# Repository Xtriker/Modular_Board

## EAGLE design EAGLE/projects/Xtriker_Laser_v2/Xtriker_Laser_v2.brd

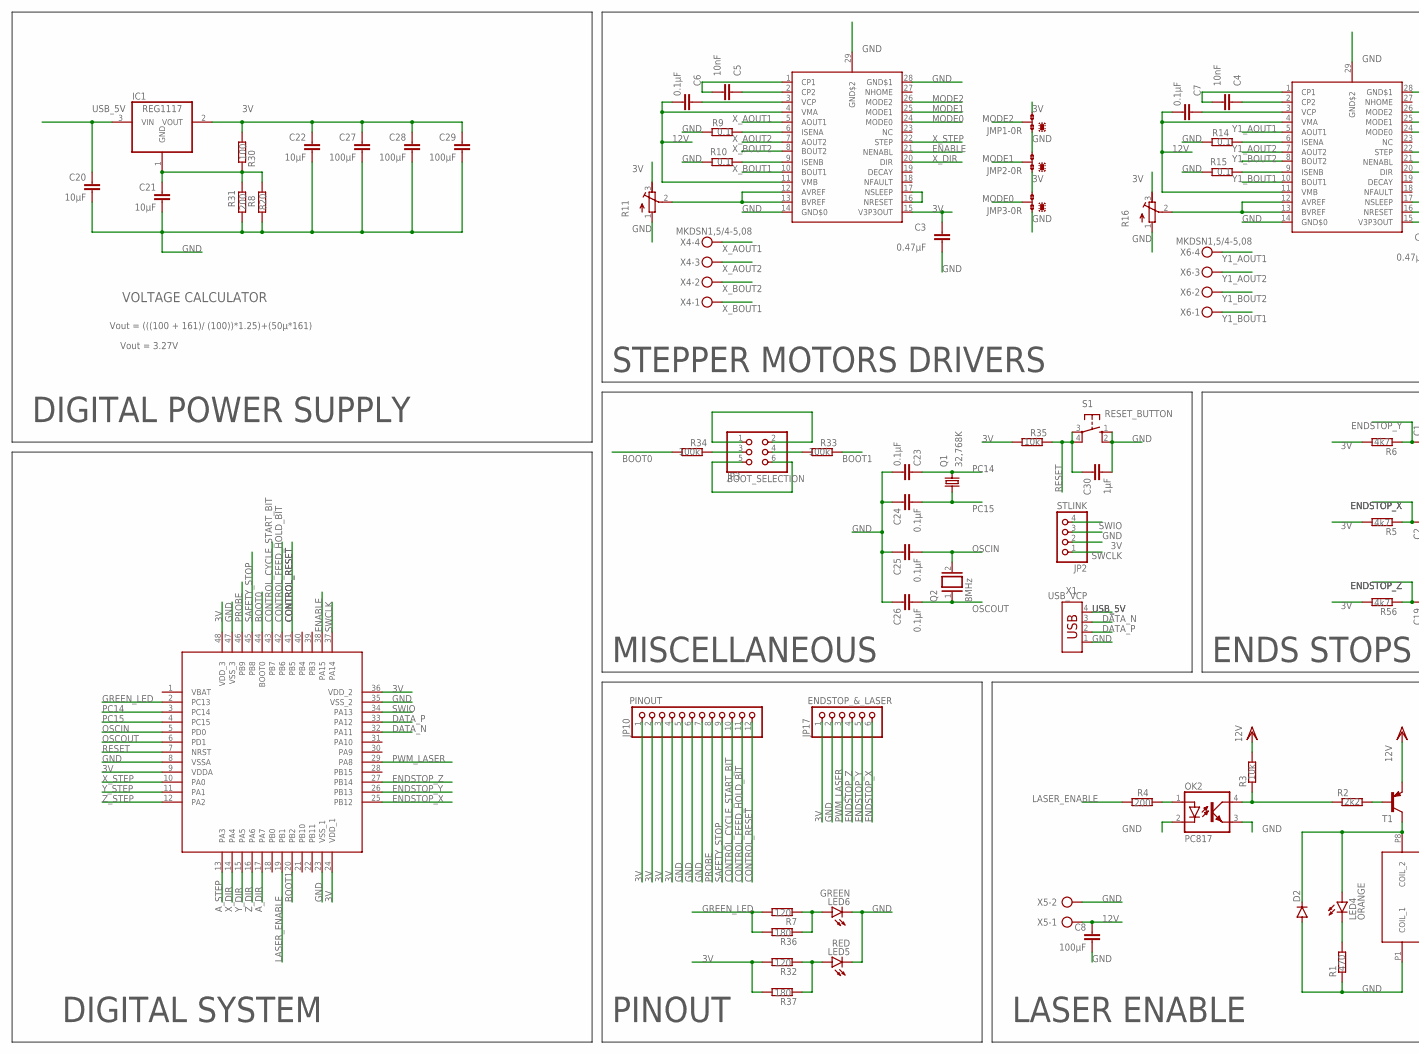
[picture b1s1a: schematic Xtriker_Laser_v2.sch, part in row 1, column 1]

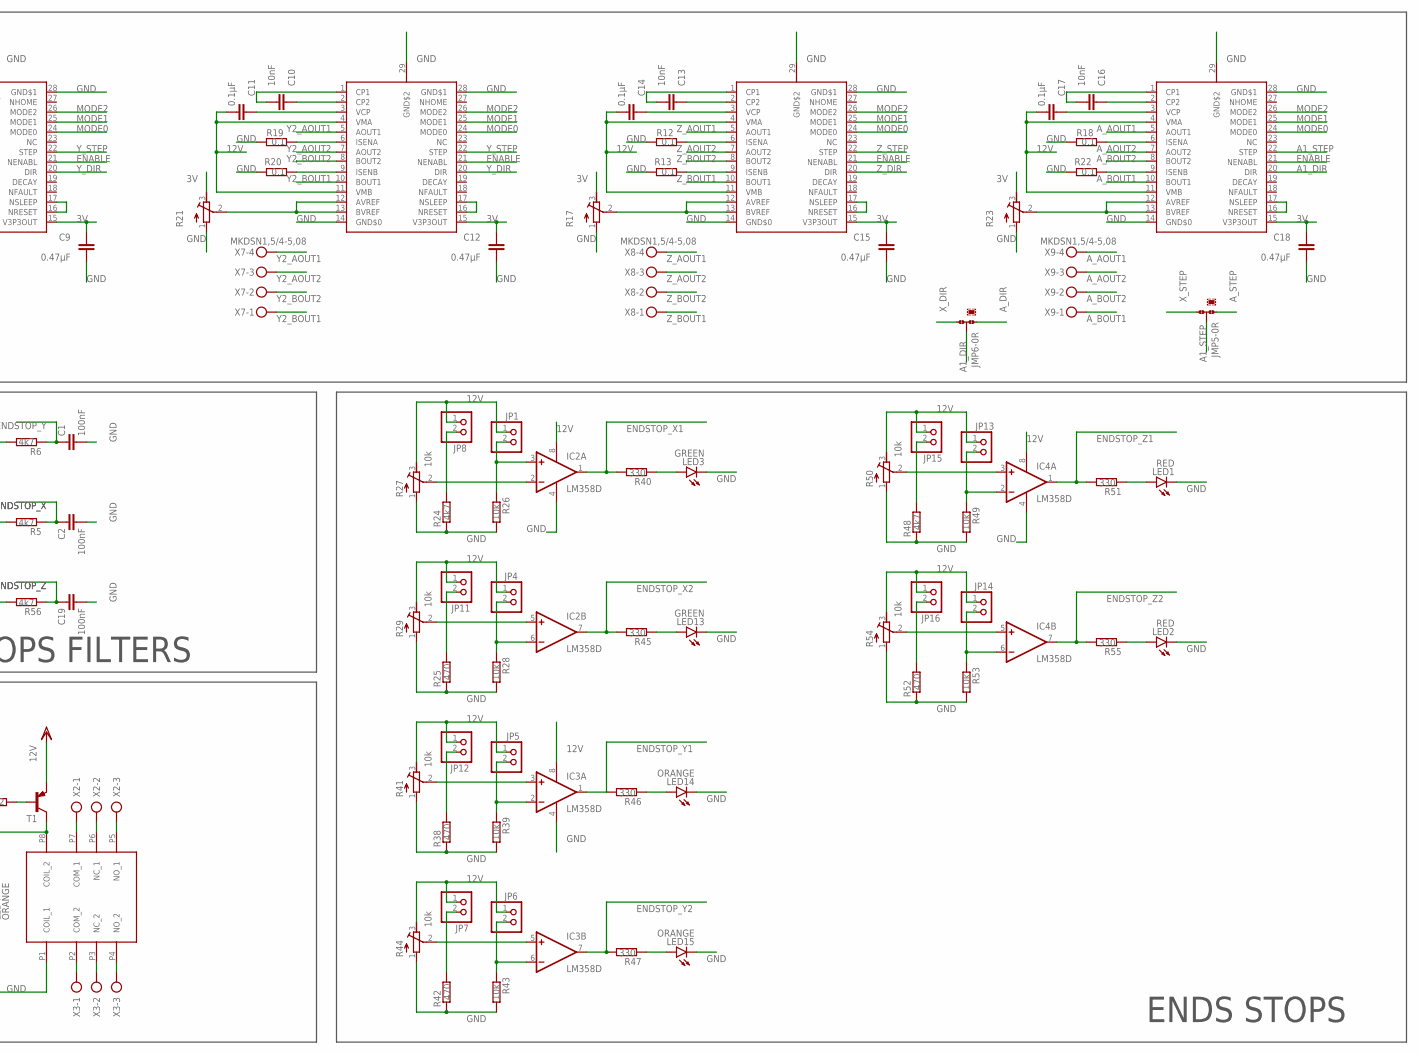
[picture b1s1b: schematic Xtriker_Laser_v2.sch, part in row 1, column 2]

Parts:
C1, C2, C19: 100nF; C0805
C3, C9, C12, C15, C18: 0.47µF; C0805
C4, C5, C10, C13, C16: 10nF; C0805
C6, C7, C11, C14, C17, C23, C24, C25, C26: 0.1µF; C0805
C8, C27, C28, C29: 100µF; C0805
C20, C21, C22: 10µF; C0805
C30: 1µF; C0805
D2: DIODE-DO214AA; DO214AA
IC1: REG1117; SOT223
IC2, IC3, IC4: LM358D; SO08
JMP1, JMP2, JMP3, JMP5, JMP6: 0R-JUMPA; A0R-JMP
JP1, JP4, JP5, JP6, JP7, JP8, JP11, JP12, JP13, JP14, JP15, JP16: PINHD-1X2; 1X02
JP2: STLINK; 1X04
JP3: BOOT_SELECTION; 2X03
JP10: PINOUT; 1X12
JP17: ENDSTOP_&_LASER; 1X06
LED1, LED2, LED5: RED; CHIP-LED0805
LED3, LED6, LED13: GREEN; CHIP-LED0805
LED4, LED14, LED15: ORANGE; CHIP-LED0805
OK2: PC817; DIL04
Q1: 32,768K; 8.2X3.8
Q2: 8MHz; QS
R1, R25, R38, R42, R52: 470; R0805
R2: 2k2; R0805
R3, R26, R28, R35, R39, R43, R49, R53: 10k; R0805
R4, R31: 200; R0805
R5, R6, R24, R48, R56: 4k7; R0805
R7, R32: 120; R0805
R8: 820; R0805
R9, R10, R12, R13, R14, R15, R18, R19, R20, R22: 0.1; R2512
R11, R16, R17, R21, R23: R-TRIMM3296W; RTRIM3296W
R27, R29, R41, R44, R50, R54: 10k; RTRIM3296W
R30: 100; R0805
R33, R34: 100k; R0805
R36, R37: 180; R0805
R40, R45, R46, R47, R51, R55: 330; R0805
S1: RESET_BUTTON; B3F-10XX
T1: -PNP-SOT23-BCE; SOT23-BCE
U$1, U$2, U$3, U$4, U$7: DRV8825; SOP65P660X135-29T310X518N
U$5: TDS-1202L; TDS_1202L
U$6: STM32F103C8_LQFP48; QFP50P900X900X160-48N
X1: USB_VCP; USB
X2, X3: AK500/3
X4, X6, X7, X8, X9: MKDSN1,5/4-5,08
X5: AK500/2

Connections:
3V: C3.1, C9.1, C12.1, C15.1, C18.1, C22.1, C27.1, C28.1, C29.1, IC1.2 (VOUT), JMP1.3, JMP2.1, JMP3.3, JP2.2, JP10.1, JP10.2, JP10.3, JP10.4, JP17.1, R5.2, R6.2, R11.3 (E), R16.3 (E), R17.3 (E), R21.3 (E), R23.3 (E), R30.2, R32.2, R35.2, R37.2, R56.2, U$1.15 (V3P3OUT), U$2.15 (V3P3OUT), U$3.15 (V3P3OUT), U$4.15 (V3P3OUT), U$6.9 (VDDA), U$6.24 (VDD_1), U$6.36 (VDD_2), U$6.48 (VDD_3), U$7.15 (V3P3OUT)
12V: C6.2, C7.2, C8.1, C11.2, C14.2, C17.2, IC2.8 (V+), IC3.8 (V+), IC4.8 (V+), JP1.1, JP4.1, JP5.1, JP6.1, JP7.1, JP8.1, JP11.1, JP12.1, JP13.1, JP14.1, JP15.1, JP16.1, R27.3 (E), R29.3 (E), R41.3 (E), R44.3 (E), R50.3 (E), R54.3 (E), U$1.4 (VMA), U$1.11 (VMB), U$2.4 (VMA), U$2.11 (VMB), U$3.4 (VMA), U$3.11 (VMB), U$4.4 (VMA), U$4.11 (VMB), U$7.4 (VMA), U$7.11 (VMB), X5.1
A1_DIR: JMP6.2, U$7.20 (DIR)
A1_STEP: JMP5.2, U$7.22 (STEP)
A_AOUT1: U$7.5 (AOUT1), X9.4
A_AOUT2: U$7.7 (AOUT2), X9.3
A_BOUT1: U$7.10 (BOUT1), X9.1
A_BOUT2: U$7.8 (BOUT2), X9.2
A_DIR: JMP6.1, U$6.17 (PA7)
A_STEP: JMP5.1, U$6.13 (PA3)
BOOT0: R34.2, U$6.44 (BOOT0)
BOOT1: R33.1, U$6.20 (PB2)
CONTROL_CYCLE_START_BIT: JP10.10, U$6.43 (PB7)
CONTROL_FEED_HOLD_BIT: JP10.11, U$6.42 (PB6)
CONTROL_RESET: JP10.12, U$6.41 (PB5)
DATA_N: U$6.32 (PA11), X1.3
DATA_P: U$6.33 (PA12), X1.2
ENABLE: U$1.21 (NENABL), U$2.21 (NENABL), U$3.21 (NENABL), U$4.21 (NENABL), U$6.38 (PA15), U$7.21 (NENABL)
ENDSTOP_X: C2.1, JP17.6, R5.1, U$6.25 (PB12)
ENDSTOP_X1: IC2.1 (OUT), R40.2
ENDSTOP_X2: IC2.7 (OUT), R45.2
ENDSTOP_Y: C1.1, JP17.5, R6.1, U$6.26 (PB13)
ENDSTOP_Y1: IC3.1 (OUT), R46.2
ENDSTOP_Y2: IC3.7 (OUT), R47.2
ENDSTOP_Z: C19.1, JP17.4, R56.1, U$6.27 (PB14)
ENDSTOP_Z1: IC4.1 (OUT), R51.2
ENDSTOP_Z2: IC4.7 (OUT), R55.2
GND: C1.2, C2.2, C3.2, C8.2, C9.2, C12.2, C15.2, C18.2, C19.2, C20.2, C21.2, C22.2, C23.2, C24.1, C25.1, C26.1, C27.2, C28.2, C29.2, C30.2, D2.A, IC2.4 (V-), IC3.4 (V-), IC4.4 (V-), JMP1.1, JMP2.3, JMP3.1, JP2.3, JP10.5, JP10.6, JP10.7, JP17.2, LED1.C, LED2.C, LED3.C, LED5.C, LED6.C, LED13.C, LED14.C, LED15.C, OK2.2 (C), OK2.3 (EMIT), R1.1, R8.1, R9.1, R10.1, R11.1 (A), R12.1, R13.1, R14.1, R15.1, R16.1 (A), R17.1 (A), R18.1, R19.1, R20.1, R21.1 (A), R22.1, R23.1 (A), R24.1, R25.1, R26.2, R27.1 (A), R28.2, R29.1 (A), R31.1, R38.1, R39.2, R41.1 (A), R42.1, R43.2, R44.1 (A), R48.1, R49.2, R50.1 (A), R52.1, R53.2, R54.1 (A), S1.1 (S), S1.2 (S1), U$1.14 (GND$0), U$1.28 (GND$1), U$1.29 (GND$2), U$2.14 (GND$0), U$2.28 (GND$1), U$2.29 (GND$2), U$3.14 (GND$0), U$3.28 (GND$1), U$3.29 (GND$2), U$4.14 (GND$0), U$4.28 (GND$1), U$4.29 (GND$2), U$5.P1 (COIL_1), U$6.8 (VSSA), U$6.23 (VSS_1), U$6.35 (VSS_2), U$6.47 (VSS_3), U$7.14 (GND$0), U$7.28 (GND$1), U$7.29 (GND$2), X1.1, X5.2
GREEN_LED: R7.2, R36.2, U$6.2 (PC13)
LASER_ENABLE: R4.1, U$6.19 (PB1)
MODE0: JMP3.2, U$1.24 (MODE0), U$2.24 (MODE0), U$3.24 (MODE0), U$4.24 (MODE0), U$7.24 (MODE0)
MODE1: JMP2.2, U$1.25 (MODE1), U$2.25 (MODE1), U$3.25 (MODE1), U$4.25 (MODE1), U$7.25 (MODE1)
MODE2: JMP1.2, U$1.26 (MODE2), U$2.26 (MODE2), U$3.26 (MODE2), U$4.26 (MODE2), U$7.26 (MODE2)
unnamed: C13.2, U$4.1 (CP1)
unnamed: U$1.16 (NRESET), U$1.17 (NSLEEP)
unnamed: C4.2, U$2.1 (CP1)
unnamed: C4.1, U$2.2 (CP2)
unnamed: C7.1, U$2.3 (VCP)
unnamed: R14.2, U$2.6 (ISENA)
unnamed: R15.2, U$2.9 (ISENB)
unnamed: R16.2 (S), U$2.12 (AVREF), U$2.13 (BVREF)
unnamed: C21.1, IC1.1 (GND), R8.2, R30.1, R31.2
unnamed: LED5.A, R32.1, R37.1
unnamed: JP3.1, JP3.2
unnamed: C13.1, U$4.2 (CP2)
unnamed: D2.C, LED4.A, T1.C, U$5.P8 (COIL_2)
unnamed: LED4.C, R1.2
unnamed: R2.2, T1.B
unnamed: OK2.4 (COL), R2.1, R3.1
unnamed: OK2.1 (A), R4.2
unnamed: U$2.16 (NRESET), U$2.17 (NSLEEP)
unnamed: C10.2, U$3.1 (CP1)
unnamed: C10.1, U$3.2 (CP2)
unnamed: C11.1, U$3.3 (VCP)
unnamed: C5.2, U$1.1 (CP1)
unnamed: C5.1, U$1.2 (CP2)
unnamed: C6.1, U$1.3 (VCP)
unnamed: R19.2, U$3.6 (ISENA)
unnamed: R20.2, U$3.9 (ISENB)
unnamed: R9.2, U$1.6 (ISENA)
unnamed: R21.2 (S), U$3.12 (AVREF), U$3.13 (BVREF)
unnamed: U$5.P7 (COM_1), X2.1
unnamed: U$5.P6 (NC_1), X2.2
unnamed: U$5.P5 (NO_1), X2.3
unnamed: U$5.P4 (NO_2), X3.3
unnamed: U$5.P3 (NC_2), X3.2
unnamed: U$5.P2 (COM_2), X3.1
unnamed: LED6.A, R7.1, R36.1
unnamed: C14.1, U$4.3 (VCP)
unnamed: R10.2, U$1.9 (ISENB)
unnamed: U$3.16 (NRESET), U$3.17 (NSLEEP)
unnamed: LED3.A, R40.1
unnamed: IC2.3 (+IN), JP1.2, R26.1
unnamed: JP3.5, JP3.6
unnamed: JP3.3, R34.1
unnamed: JP3.4, R33.2
unnamed: R11.2 (S), U$1.12 (AVREF), U$1.13 (BVREF)
unnamed: JP8.2, R24.2
unnamed: IC2.6 (-IN), JP4.2, R28.1
unnamed: IC2.2 (-IN), R27.2 (S)
unnamed: JP11.2, R25.2
unnamed: IC2.5 (+IN), R29.2 (S)
unnamed: IC3.2 (-IN), JP5.2, R39.1
unnamed: JP12.2, R38.2
unnamed: IC3.3 (+IN), R41.2 (S)
unnamed: IC3.6 (-IN), JP6.2, R43.1
unnamed: JP7.2, R42.2
unnamed: IC3.5 (+IN), R44.2 (S)
unnamed: LED13.A, R45.1
unnamed: LED14.A, R46.1
unnamed: LED15.A, R47.1
unnamed: R12.2, U$4.6 (ISENA)
unnamed: R13.2, U$4.9 (ISENB)
unnamed: R17.2 (S), U$4.12 (AVREF), U$4.13 (BVREF)
unnamed: U$4.16 (NRESET), U$4.17 (NSLEEP)
unnamed: C16.2, U$7.1 (CP1)
unnamed: C16.1, U$7.2 (CP2)
unnamed: C17.1, U$7.3 (VCP)
unnamed: R18.2, U$7.6 (ISENA)
unnamed: R22.2, U$7.9 (ISENB)
unnamed: R23.2 (S), U$7.12 (AVREF), U$7.13 (BVREF)
unnamed: U$7.16 (NRESET), U$7.17 (NSLEEP)
unnamed: IC4.2 (-IN), JP13.2, R49.1
unnamed: JP15.2, R48.2
unnamed: IC4.3 (+IN), R50.2 (S)
unnamed: LED1.A, R51.1
unnamed: IC4.6 (-IN), JP14.2, R53.1
unnamed: JP16.2, R52.2
unnamed: IC4.5 (+IN), R54.2 (S)
unnamed: LED2.A, R55.1
OSCIN: C25.2, Q2.2, U$6.5 (PD0)
OSCOUT: C26.2, Q2.1, U$6.6 (PD1)
PC14: C23.1, Q1.4 (2), U$6.3 (PC14)
PC15: C24.2, Q1.1, U$6.4 (PC15)
PROBE: JP10.8, U$6.46 (PB9)
PWM_LASER: JP17.3, U$6.29 (PA8)
RESET: C30.1, R35.1, S1.3, S1.4 (P1), U$6.7 (NRST)
SAFETY_STOP: JP10.9, U$6.45 (PB8)
SWCLK: JP2.1, U$6.37 (PA14)
SWIO: JP2.4, U$6.34 (PA13)
USB_5V: C20.1, IC1.3 (VIN), X1.4
VDD: R3.2, T1.E
X_AOUT1: U$1.5 (AOUT1), X4.4
X_AOUT2: U$1.7 (AOUT2), X4.3
X_BOUT1: U$1.10 (BOUT1), X4.1
X_BOUT2: U$1.8 (BOUT2), X4.2
X_DIR: JMP6.3, U$1.20 (DIR), U$6.14 (PA4)
X_STEP: JMP5.3, U$1.22 (STEP), U$6.10 (PA0)
Y1_AOUT1: U$2.5 (AOUT1), X6.4
Y1_AOUT2: U$2.7 (AOUT2), X6.3
Y1_BOUT1: U$2.10 (BOUT1), X6.1
Y1_BOUT2: U$2.8 (BOUT2), X6.2
Y2_AOUT1: U$3.5 (AOUT1), X7.4
Y2_AOUT2: U$3.7 (AOUT2), X7.3
Y2_BOUT1: U$3.10 (BOUT1), X7.1
Y2_BOUT2: U$3.8 (BOUT2), X7.2
Y_DIR: U$2.20 (DIR), U$3.20 (DIR), U$6.15 (PA5)
Y_STEP: U$2.22 (STEP), U$3.22 (STEP), U$6.11 (PA1)
Z_AOUT1: U$4.5 (AOUT1), X8.4
Z_AOUT2: U$4.7 (AOUT2), X8.3
Z_BOUT1: U$4.10 (BOUT1), X8.1
Z_BOUT2: U$4.8 (BOUT2), X8.2
Z_DIR: U$4.20 (DIR), U$6.16 (PA6)
Z_STEP: U$4.22 (STEP), U$6.12 (PA2)

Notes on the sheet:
ENDS STOPS FILTERS
MISCELLANEOUS
LASER ENABLE
STEPPER MOTORS DRIVERS
PINOUT
DIGITAL POWER SUPPLY
DIGITAL SYSTEM
Vout = (((100 + 161)/ (100))*1.25)+(50µ*161)
Vout = 3.27V
VOLTAGE CALCULATOR
ENDS STOPS

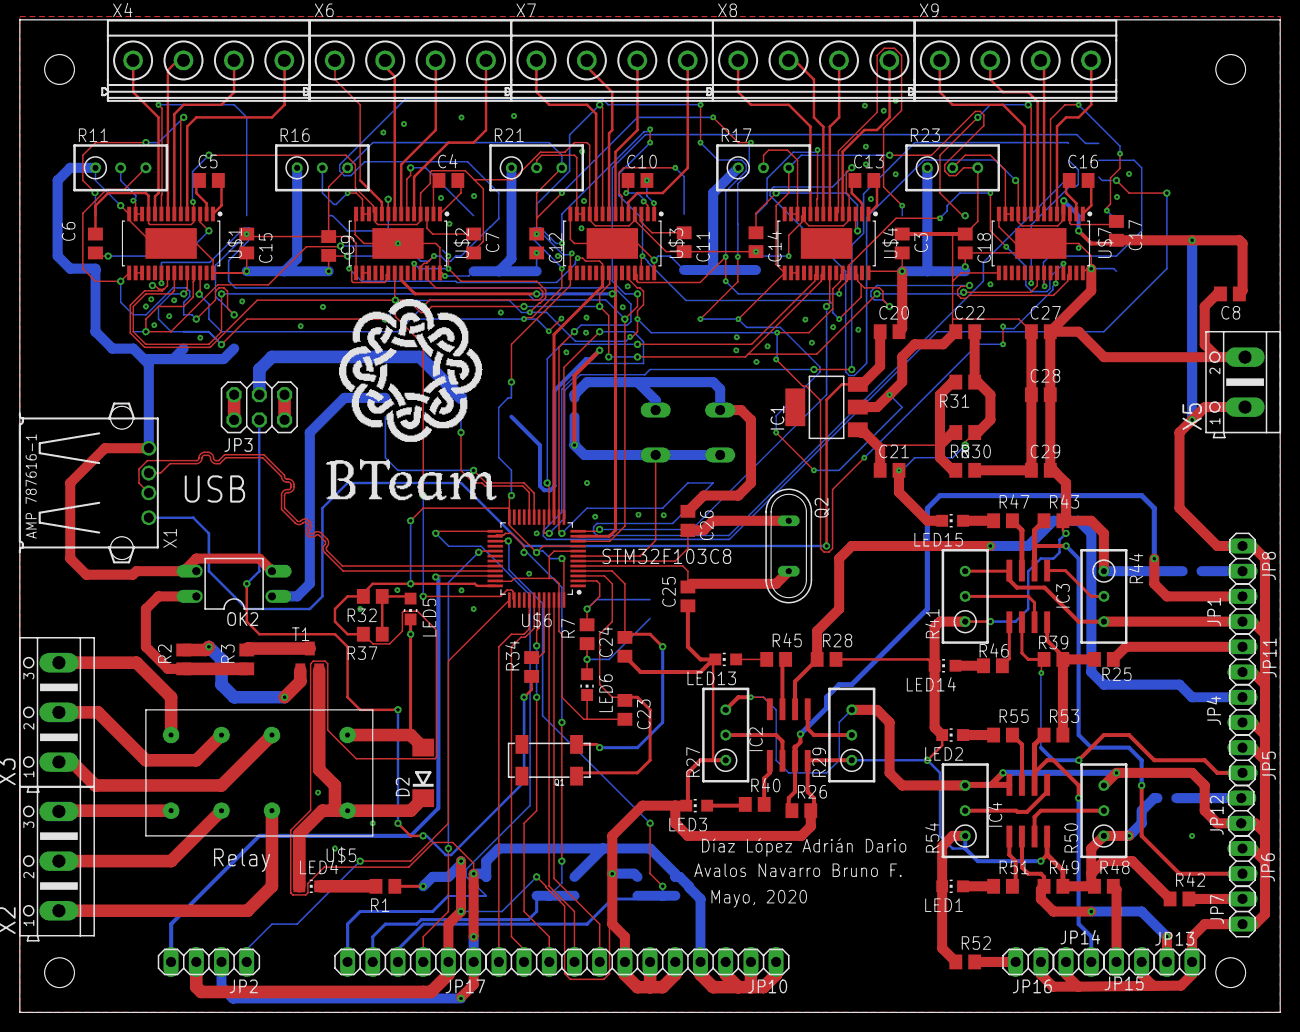
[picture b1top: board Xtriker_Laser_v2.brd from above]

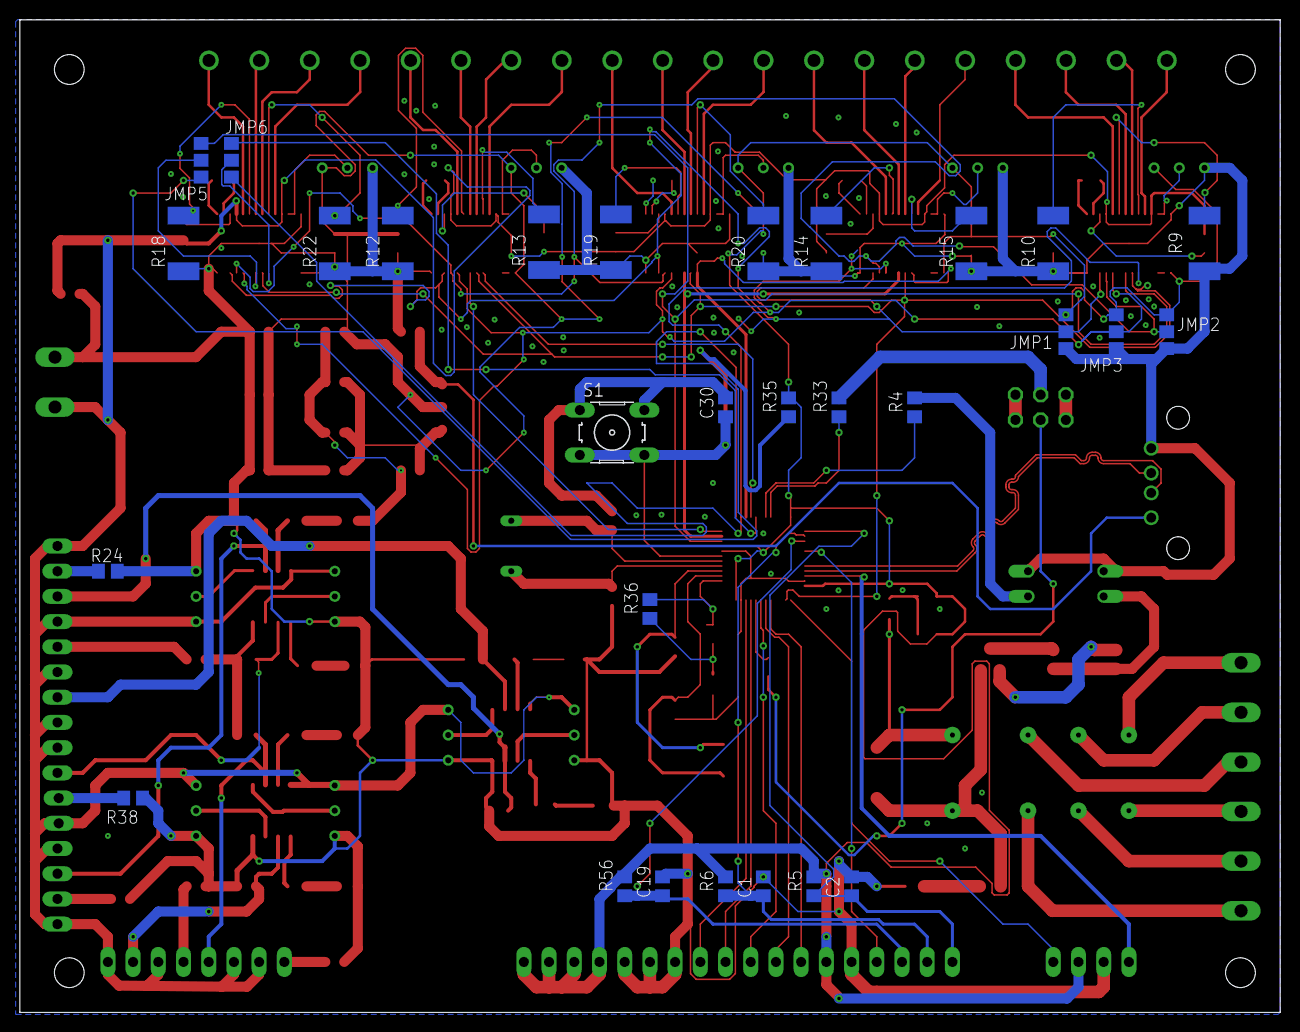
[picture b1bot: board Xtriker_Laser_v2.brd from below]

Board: 2 copper layers, 127.0 x 100.0 mm, 142 parts (29 on the bottom side), 144 nets.

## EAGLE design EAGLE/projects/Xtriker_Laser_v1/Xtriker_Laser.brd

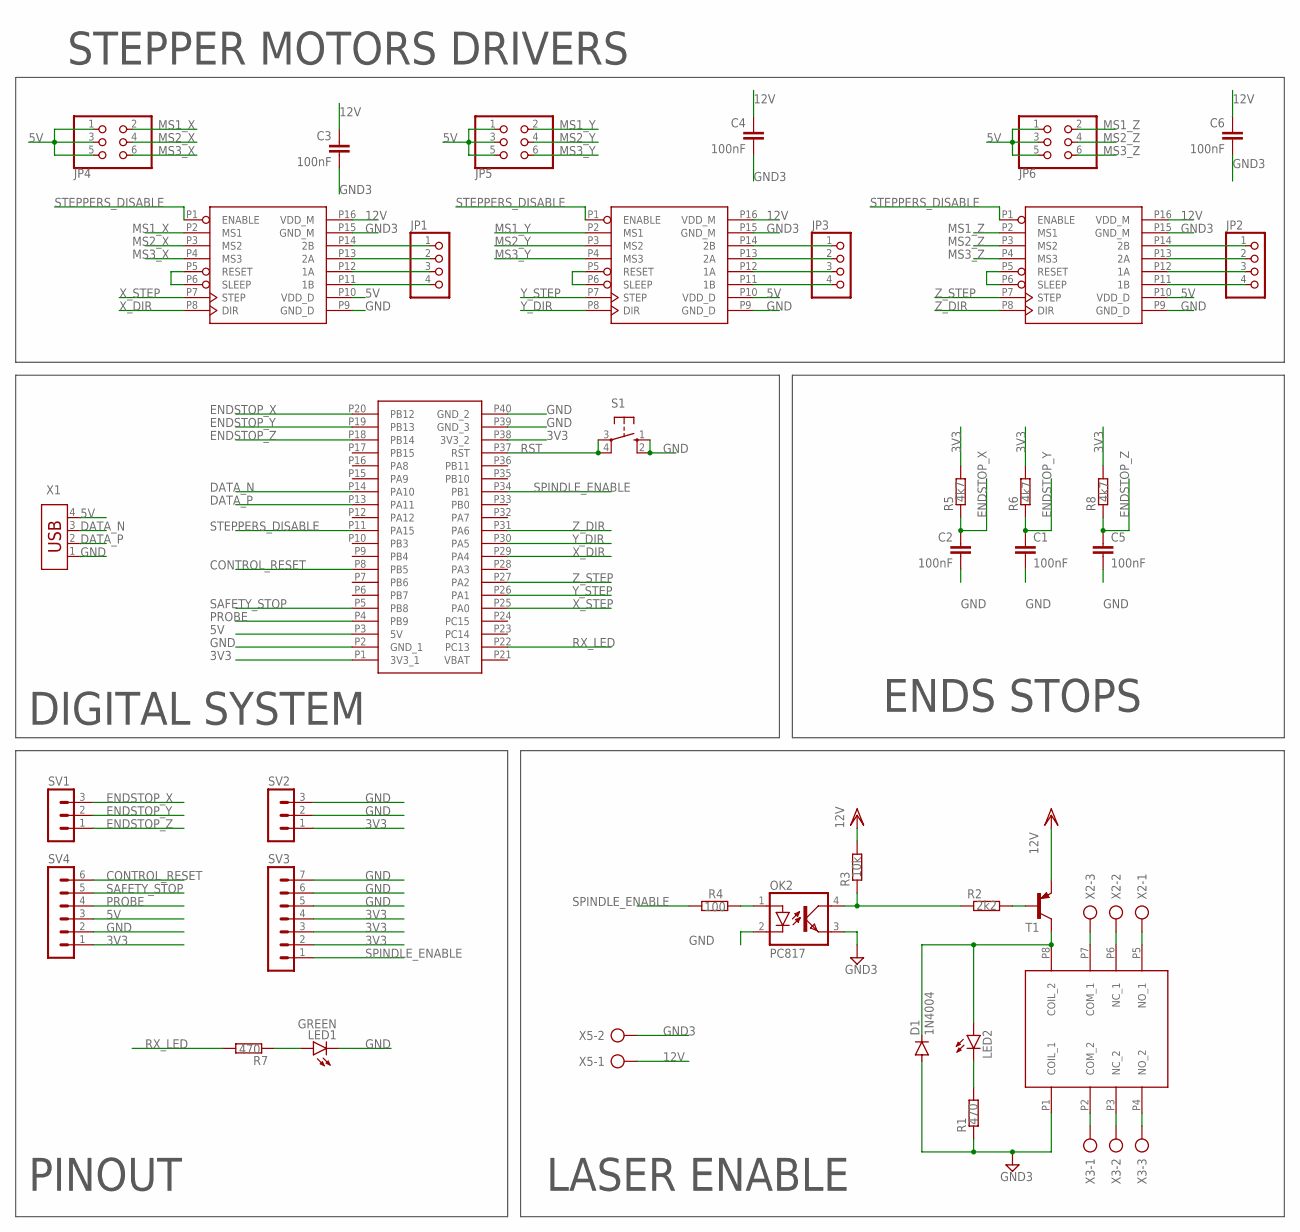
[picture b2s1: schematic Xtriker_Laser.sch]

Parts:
C1, C2, C3, C4, C5, C6: 100nF; C0805
D1: 1N4004; DO41-10
JP1, JP2, JP3: PINHD-1X4; 1X04
JP4, JP5, JP6: PINHD-2X3; 2X03
LED1: GREEN; LED3MM
LED2: LED3MM
OK2: PC817; DIL04
R1, R7: 470; R0805
R2: 2k2; R0805
R3: 10k; R0805
R4: 100; R0805
R5, R6, R8: 4k7; R0805
S1: 10-XX; B3F-10XX
SV1, SV2: MA03-1
SV3: MA07-1
SV4: MA06-1
T1: -PNP-SOT23-BCE; SOT23-BCE
U$1, U$2, U$3: A4988
U$4: BLUEPILL_STM32F103C8
U$5: TDS-1202L; TDS_1202L
X1: USB-787616; USB
X2, X3: AK500/3
X5: AK500/2

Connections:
3V3: R5.2, R6.2, R8.2, SV2.1, SV3.2, SV3.3, SV3.4, SV4.1, U$4.P1 (3V3_1), U$4.P38 (3V3_2)
5V: JP4.1, JP4.3, JP4.5, JP5.1, JP5.3, JP5.5, JP6.1, JP6.3, JP6.5, SV4.3, U$1.P10 (VDD_D), U$2.P10 (VDD_D), U$3.P10 (VDD_D), U$4.P3 (5V), X1.4
12V: C3.1, C4.1, C6.1, U$1.P16 (VDD_M), U$2.P16 (VDD_M), U$3.P16 (VDD_M), X5.1
CONTROL_RESET: SV4.6, U$4.P8 (PB5)
DATA_N: U$4.P14 (PA10), X1.3
DATA_P: U$4.P13 (PA11), X1.2
ENDSTOP_X: C2.1, R5.1, SV1.3, U$4.P20 (PB12)
ENDSTOP_Y: C1.1, R6.1, SV1.2, U$4.P19 (PB13)
ENDSTOP_Z: C5.1, R8.1, SV1.1, U$4.P18 (PB14)
GND: C1.2, C2.2, C5.2, LED1.K (C), OK2.2 (C), S1.1 (S), S1.2 (S1), SV2.2, SV2.3, SV3.5, SV3.6, SV3.7, SV4.2, U$1.P9 (GND_D), U$2.P9 (GND_D), U$3.P9 (GND_D), U$4.P2 (GND_1), U$4.P39 (GND_3), U$4.P40 (GND_2), X1.1
GND3: C3.2, C4.2, C6.2, D1.A, OK2.3 (EMIT), R1.1, U$1.P15 (GND_M), U$2.P15 (GND_M), U$3.P15 (GND_M), U$5.P1 (COIL_1), X5.2
MS1_X: JP4.2, U$1.P2 (MS1)
MS1_Y: JP5.2, U$3.P2 (MS1)
MS1_Z: JP6.2, U$2.P2 (MS1)
MS2_X: JP4.4, U$1.P3 (MS2)
MS2_Y: JP5.4, U$3.P3 (MS2)
MS2_Z: JP6.4, U$2.P3 (MS2)
MS3_X: JP4.6, U$1.P4 (MS3)
MS3_Y: JP5.6, U$3.P4 (MS3)
MS3_Z: JP6.6, U$2.P4 (MS3)
unnamed: JP2.4, U$2.P11 (1B)
unnamed: JP2.3, U$2.P12 (1A)
unnamed: JP2.2, U$2.P13 (2A)
unnamed: JP2.1, U$2.P14 (2B)
unnamed: JP3.4, U$3.P11 (1B)
unnamed: JP3.3, U$3.P12 (1A)
unnamed: JP3.2, U$3.P13 (2A)
unnamed: JP3.1, U$3.P14 (2B)
unnamed: JP1.4, U$1.P11 (1B)
unnamed: JP1.3, U$1.P12 (1A)
unnamed: JP1.2, U$1.P13 (2A)
unnamed: D1.C, LED2.A, T1.C, U$5.P8 (COIL_2)
unnamed: LED2.K (C), R1.2
unnamed: R2.2, T1.B
unnamed: OK2.4 (COL), R2.1, R3.1
unnamed: OK2.1 (A), R4.2
unnamed: U$1.P5 (RESET), U$1.P6 (SLEEP)
unnamed: U$3.P5 (RESET), U$3.P6 (SLEEP)
unnamed: U$2.P5 (RESET), U$2.P6 (SLEEP)
unnamed: U$5.P5 (NO_1), X2.1
unnamed: U$5.P6 (NC_1), X2.2
unnamed: U$5.P7 (COM_1), X2.3
unnamed: U$5.P4 (NO_2), X3.3
unnamed: U$5.P3 (NC_2), X3.2
unnamed: U$5.P2 (COM_2), X3.1
unnamed: LED1.A, R7.1
PROBE: SV4.4, U$4.P4 (PB9)
RST: S1.3, S1.4 (P1), U$4.P37 (RST)
RX_LED: R7.2, U$4.P22 (PC13)
SAFETY_STOP: SV4.5, U$4.P5 (PB8)
SMX_2B: JP1.1, U$1.P14 (2B)
SPINDLE_ENABLE: R4.1, SV3.1, U$4.P34 (PB1)
STEPPERS_DISABLE: U$1.P1 (ENABLE), U$2.P1 (ENABLE), U$3.P1 (ENABLE), U$4.P11 (PA15)
VBAT: U$4.P21 (VBAT)
VDD: R3.2, T1.E
X_DIR: U$1.P8 (DIR), U$4.P29 (PA4)
X_STEP: U$1.P7 (STEP), U$4.P25 (PA0)
Y_DIR: U$3.P8 (DIR), U$4.P30 (PA5)
Y_STEP: U$3.P7 (STEP), U$4.P26 (PA1)
Z_DIR: U$2.P8 (DIR), U$4.P31 (PA6)
Z_STEP: U$2.P7 (STEP), U$4.P27 (PA2)

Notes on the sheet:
ENDS STOPS
DIGITAL SYSTEM
LASER ENABLE
STEPPER MOTORS DRIVERS
PINOUT

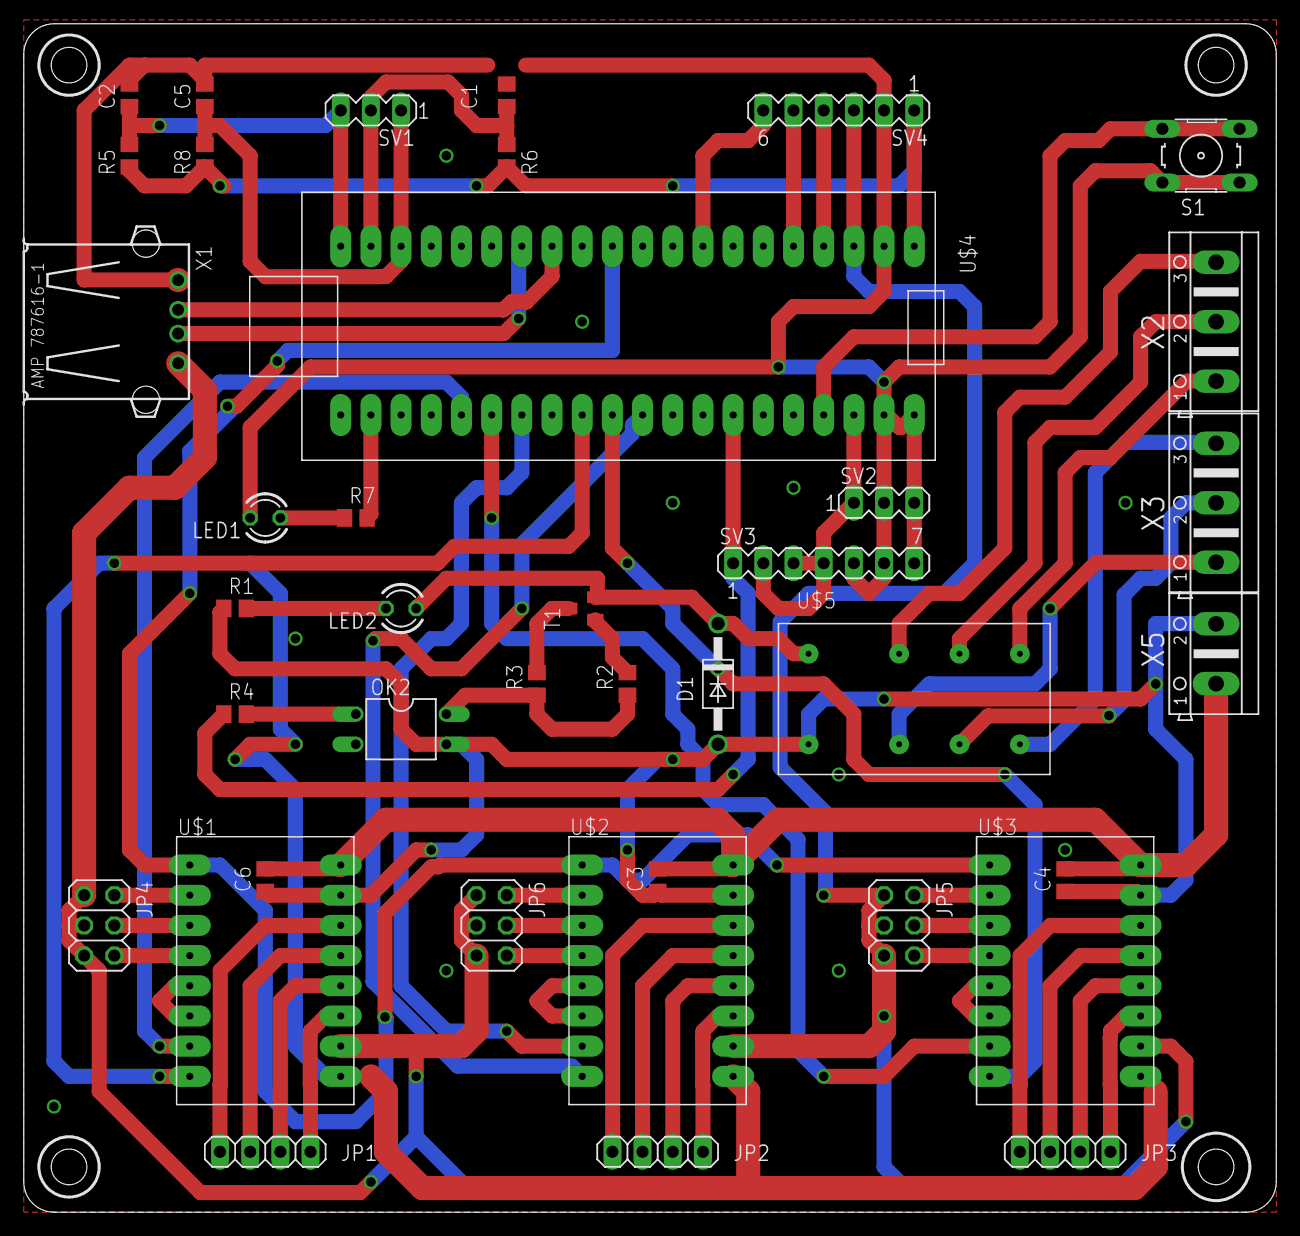
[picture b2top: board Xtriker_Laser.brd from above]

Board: 2 copper layers, 105.4 x 100.0 mm, 39 parts (0 on the bottom side), 60 nets.

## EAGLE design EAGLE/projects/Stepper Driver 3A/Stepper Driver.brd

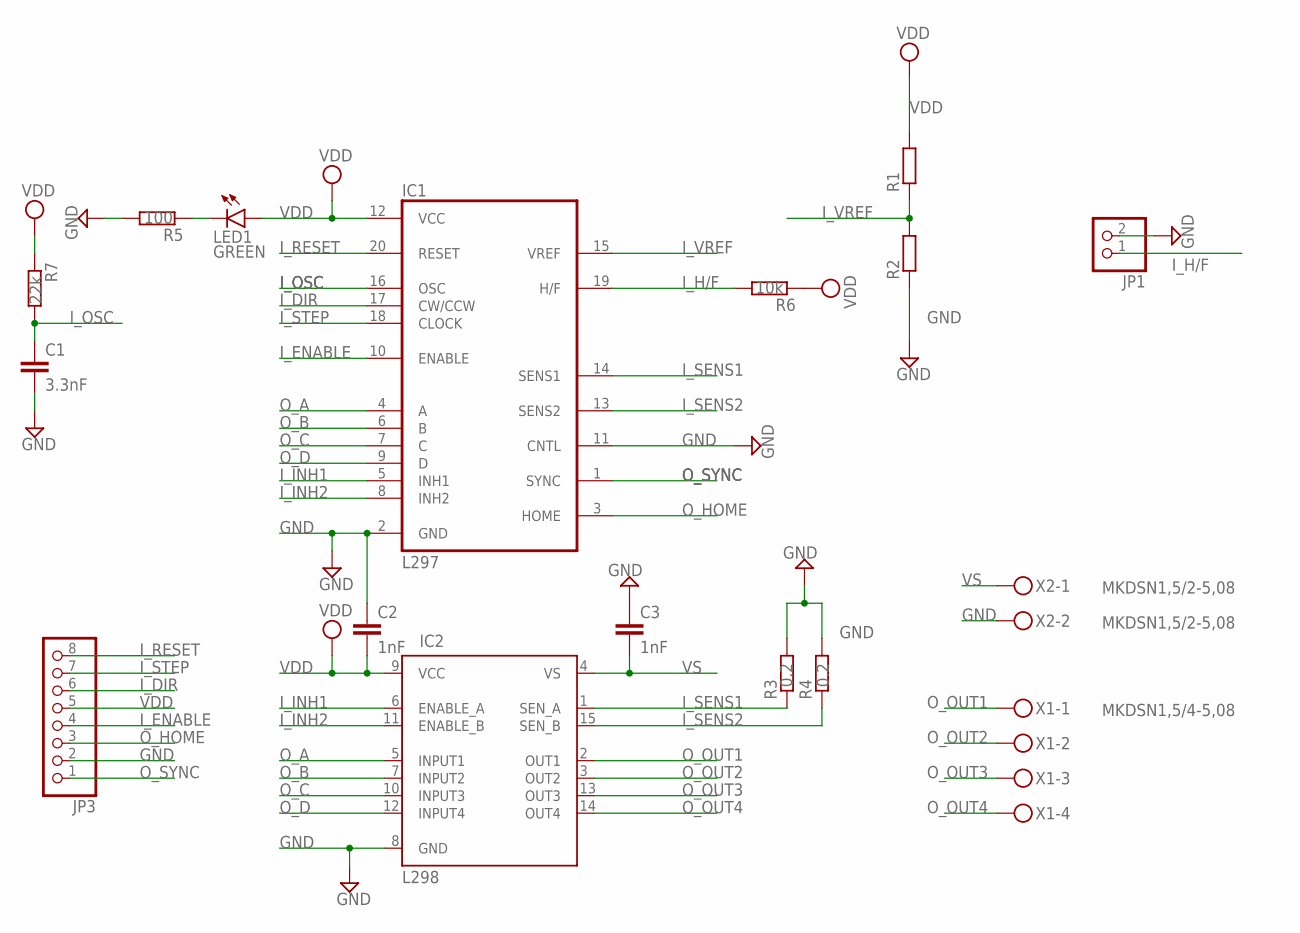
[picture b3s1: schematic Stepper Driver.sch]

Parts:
C1: 3.3nF; C0805K
C2, C3: 1nF; C0805K
IC1: L297; DIL20
IC2: L298; MULTIWATT-15
JP1: PINHD-1X2; 1X02
JP3: PINHD-1X8; 1X08
LED1: GREEN; LED5MM
R1, R2: R-EU_R0805; R0805
R3, R4: 0.2; R2512
R5: 100; R0805
R6: 10k; R0805
R7: 22k; R0805
X1: MKDSN1,5/4-5,08
X2: MKDSN1,5/2-5,08

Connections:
GND: C1.2, C2.1, C3.1, IC1.2 (GND), IC1.11 (CNTL), IC2.8 (GND), JP1.2, JP3.2, R2.1, R3.2, R4.2, R5.2, X2.2
I_DIR: IC1.17 (CW/CCW), JP3.6
I_ENABLE: IC1.10 (ENABLE), JP3.4
I_H/F: IC1.19 (H/F), JP1.1, R6.2
I_INH1: IC1.5 (INH1), IC2.6 (ENABLE_A)
I_INH2: IC1.8 (INH2), IC2.11 (ENABLE_B)
I_OSC: C1.1, IC1.16 (OSC), R7.2
I_RESET: IC1.20 (RESET), JP3.8
I_SENS1: IC1.14 (SENS1), IC2.1 (SEN_A), R3.1
I_SENS2: IC1.13 (SENS2), IC2.15 (SEN_B), R4.1
I_STEP: IC1.18 (CLOCK), JP3.7
I_VREF: IC1.15 (VREF), R1.1, R2.2
unnamed: LED1.K (C), R5.1
O_A: IC1.4 (A), IC2.5 (INPUT1)
O_B: IC1.6 (B), IC2.7 (INPUT2)
O_C: IC1.7 (C), IC2.10 (INPUT3)
O_D: IC1.9 (D), IC2.12 (INPUT4)
O_HOME: IC1.3 (HOME), JP3.3
O_OUT1: IC2.2 (OUT1), X1.1
O_OUT2: IC2.3 (OUT2), X1.2
O_OUT3: IC2.13 (OUT3), X1.3
O_OUT4: IC2.14 (OUT4), X1.4
O_SYNC: IC1.1 (SYNC), JP3.1
VDD: C2.2, IC1.12 (VCC), IC2.9 (VCC), JP3.5, LED1.A, R1.2, R6.1, R7.1
VS: C3.2, IC2.4 (VS), X2.1

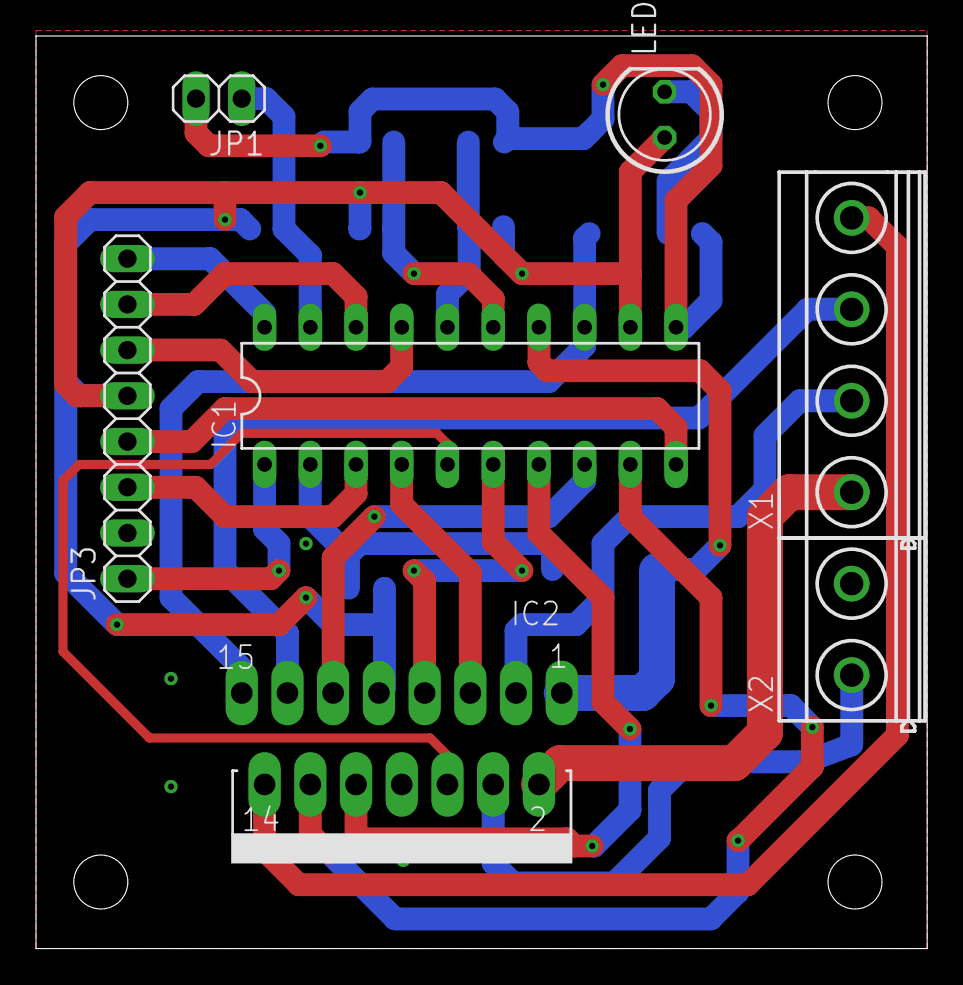
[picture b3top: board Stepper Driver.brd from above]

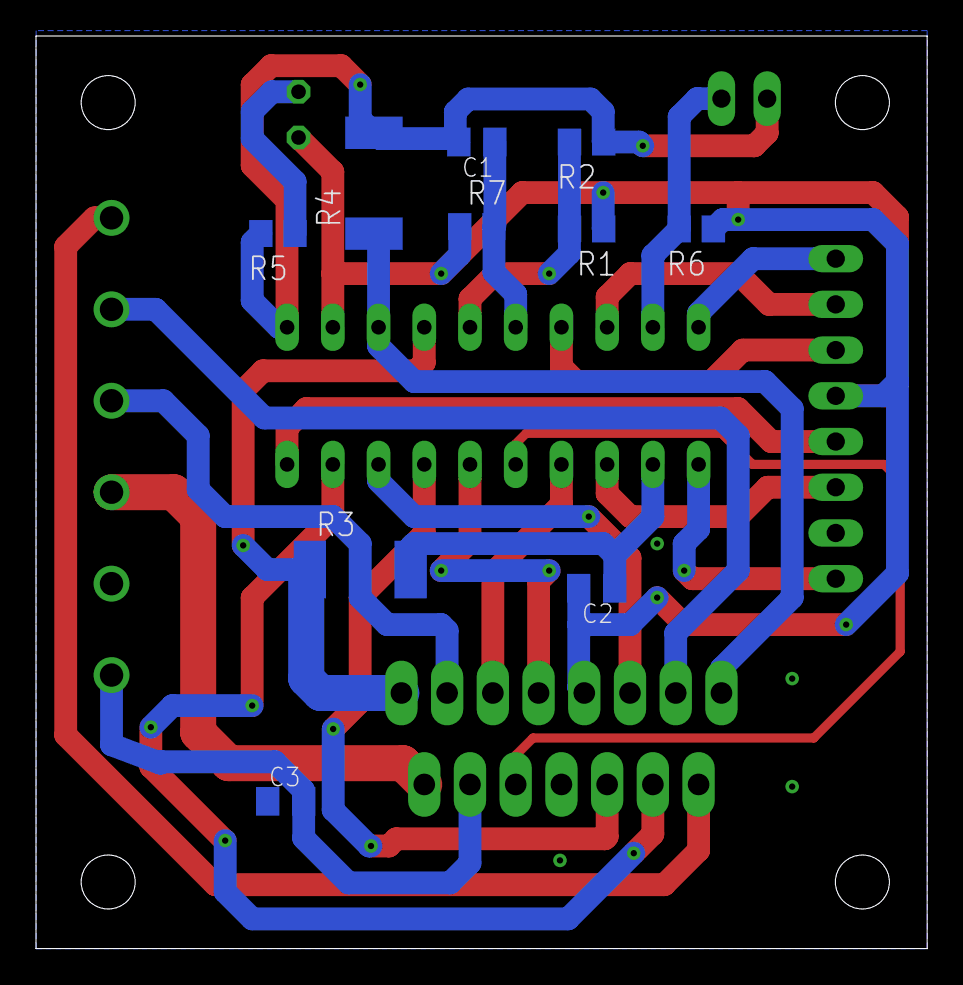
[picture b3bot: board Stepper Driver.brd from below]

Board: 2 copper layers, 49.5 x 50.7 mm, 17 parts (10 on the bottom side), 25 nets.

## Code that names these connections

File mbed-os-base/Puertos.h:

/* Definicion de los puertos */
/* Finales de carrera opticos se usan entradas digitales */

#define Endstop_X1 PTC0
#define Endstop_X2 PTC1
#define Endstop_Y1 PTC2
#define Endstop_Y2 PTC3


/* Defincon de los puertos de salida del Driver X */

#define Step_PIN_X PTD0         
#define Direction_PIN_X PTC16

/* Definicion de los puertos de salida del Driver Y1 */

#define Step_PIN_Y1 PTD5
#define Direction_PIN_Y1 PTC13

/*Definicion de los puertos de salida del Driver Y2 */

#define Step_PIN_Y2 PTA13
#define Direction_PIN_Y2 PTA16

/* Habilita los motores a pasos */

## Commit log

2020-04-30 Anexo de los .brd y los esquematicos
2020-04-30 Cambios en tamaño de las pistas
2020-04-30 Añadido pistas del Microcontrolador
2020-05-04 Pre terminado de inserción de pistas
2020-05-05 Ruteado completo de la PCB
2020-05-10 Etiquetado y logo
2020-05-10 Anexo de la plantilla para la documentación
2020-05-10 Documento Generación de archivos Gerber
2020-05-10 Documentación: modificación del documento
2020-05-10 Modificación de la documentación
2020-05-10 Documentación: BOM list & T10
2020-05-10 Descripción de proceso de generación de archivos
2020-05-10 Modificación datos personales
2020-05-15 Proyecto Mbed modular
2020-05-16 Se añade soporte del encoder eje Y
2020-05-21 Se realiza cambio de Mbed Studio a Visual Studio Code
2020-05-21 Se agrega documentación de la trjeta
2020-05-22 Modificación y prueba física del movimiento de los motores a pasos
2020-05-22 Curva de calibracion mm vs pasos
2020-05-24 Eje X&Y y finales de carrera
    Prueba de los ejes X y Y, y los finales de carrera; se sube la documentación sobre la maquina de estados usada, además de la curva de calibración de la distancia de los motores conforme a los parámet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
2020-05-25 Se organiza las librerías en la carpeta Aplicaciones
    Se realiza la inserción de la librería rtos.h para implementarla en un futuro en la tarjeta de desarrollo
2020-05-27 Se usa el segundo final de carrera.
    Se sigue trabajando en Mbed
2020-05-28 Movimiento en paralelo de los motores
2020-05-28 Documentación algoritmo curva de aceleración
2020-05-28 Ecuaciones importantes para el calculo de aceleración lineal
2020-05-28 Ecuaciones para implementar en el microcontrolador
2020-05-29 Se realiza cambio de la ecuación de distancia
    Se hace cambio de la ecuación de distancia en mm de ambos eje, se sube la documentación de la ecuación y esta en espera la implementación del sistema de control de la aceleración.
2020-05-29 Se anexa ecuación de distancia
    Se coloca un archivo .xls donde se realizaron los respectivos cálculos de la maquina para determinar los respectivos pasos por mm.

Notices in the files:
parts and their libraries:
crystal-geyer_V1_0: Copyright: Geyer-Electronic
